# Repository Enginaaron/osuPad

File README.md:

# osu!Pad
This is my design for my highway hackpad, the osu!Pad! I'm using it as the ultimate device to play the rhythm game osu!, comprising of multiple controls the user can use to play and navigate the game using their osu!Pad!
I decided to do this starter project as I found it as an excellent opportunity to familiarize myself with the process of designing PCBs and utilizing CAD software, while still providing myself with an excellent tool I can use to play osu!

# Schematic and PCBs

# CAD

# Components
- 5x Cherry MX Switches
- 1x XIAO RP2040
- 5x Keycaps
- 2x EC11 Rotary Encoder
- Custom 3D printed Top Case
- Custom 3D Printed Bottom Case

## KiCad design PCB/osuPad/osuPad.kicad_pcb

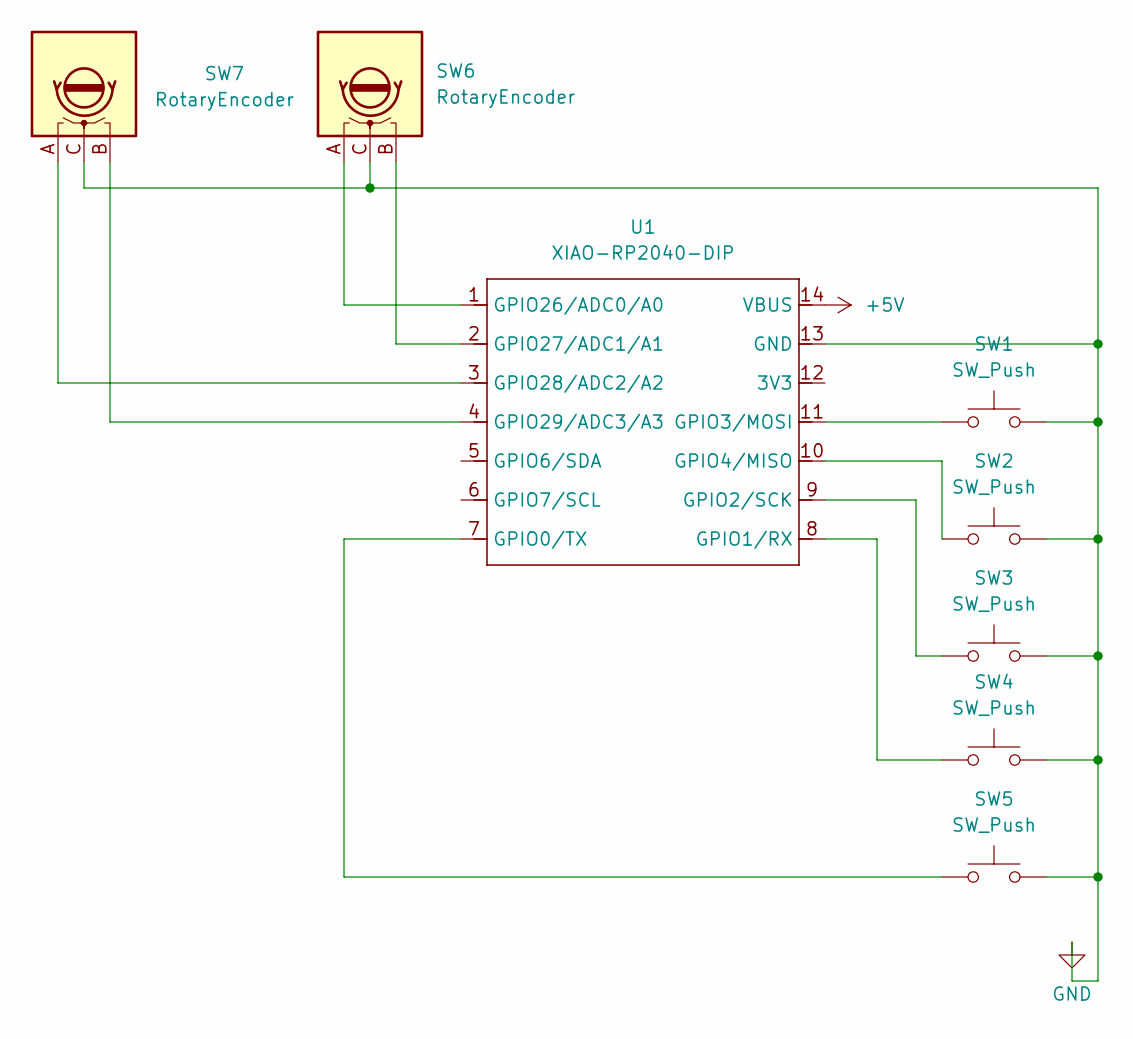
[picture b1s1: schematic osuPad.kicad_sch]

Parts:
SW1, SW2, SW3, SW4, SW5: SW_Push; SW_Cherry_MX_1.00u_PCB
SW6, SW7: RotaryEncoder; RotaryEncoder_Alps_EC11E_Vertical_H20mm
U1: XIAO-RP2040-DIP

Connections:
+5V: U1.14 (VBUS)
GND: SW1.2, SW2.2, SW3.2, SW4.2, SW5.2, SW6.C, SW7.C, U1.13 (GND)
unnamed: SW5.1, U1.7 (GPIO0/TX)
unnamed: SW4.1, U1.8 (GPIO1/RX)
unnamed: SW3.1, U1.9 (GPIO2/SCK)
unnamed: SW1.1, U1.11 (GPIO3/MOSI)
unnamed: SW2.1, U1.10 (GPIO4/MISO)
unnamed: SW6.A, U1.1 (GPIO26/ADC0/A0)
unnamed: SW6.B, U1.2 (GPIO27/ADC1/A1)
unnamed: SW7.A, U1.3 (GPIO28/ADC2/A2)
unnamed: SW7.B, U1.4 (GPIO29/ADC3/A3)

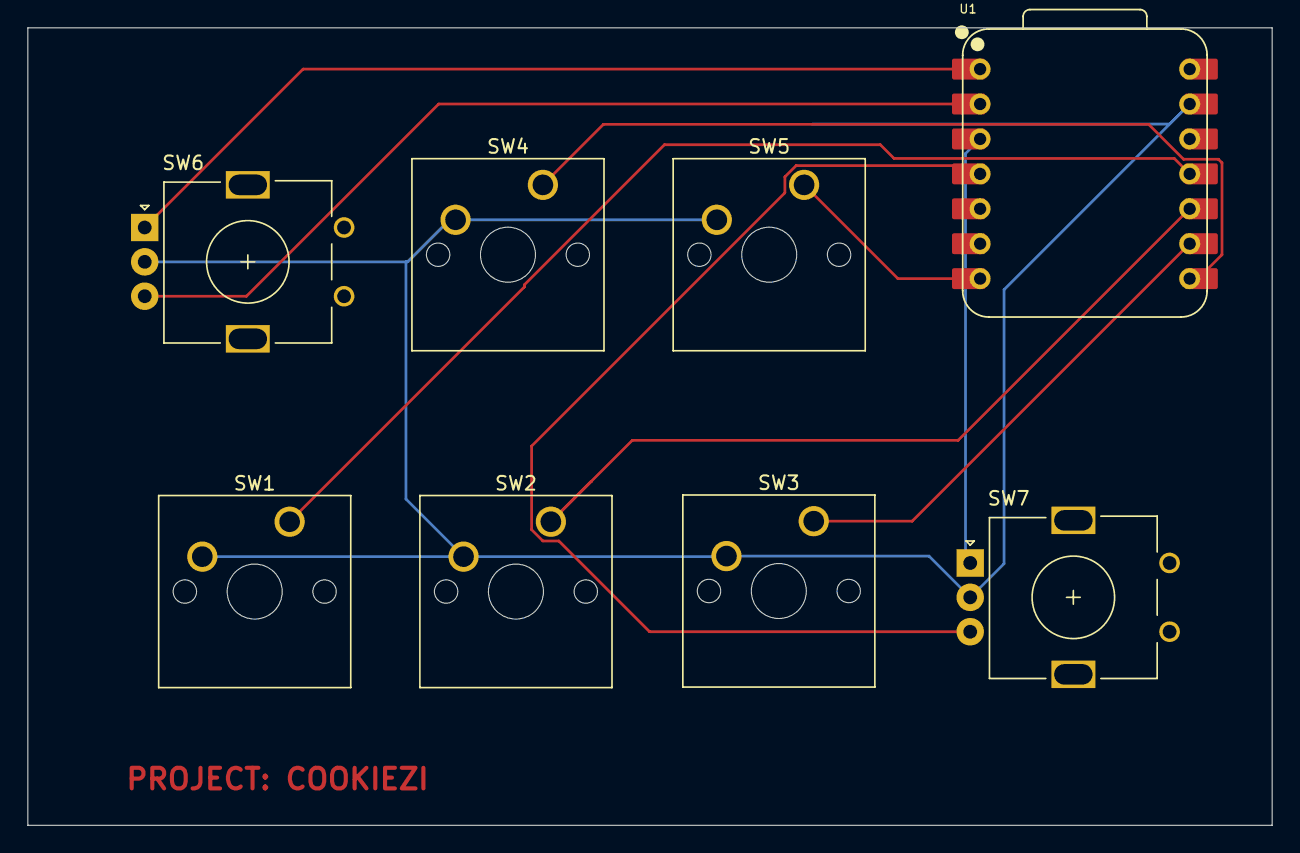
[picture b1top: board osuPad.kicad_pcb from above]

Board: 2 copper layers, 90.5 x 58.0 mm, 8 parts (0 on the bottom side), 10 nets.

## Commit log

2025-07-04 initialized files
2025-07-08 export case as step file
2025-07-08 upload cad designs, upd readme
2025-07-08 Create JOURNAL
2025-07-08 Update JOURNAL
2025-07-08 files reorganized and gerbers upl
2025-07-08 firmware code upl
2025-07-08 removed unnecessary license files
2025-07-08 Rename JOURNAL to JOURNAL.md
